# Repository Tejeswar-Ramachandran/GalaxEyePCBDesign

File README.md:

# GalaxEyePCBDesign
Internship Task for GalaxEye Space

GALAXEYE SPACE

INTERNSHIP TASK

Problem Statement:
1. You need to be able to convert inputs from up to 4 different digital I/O pins and get an output of 24 GPIO pins with a different logic level.
2. You need to design a neatly labeled schematic of this design and also generate a BOM with links to in-stock parts

Solution:

The Microcontroller will send out values at 3.3V level, from 4 different digital I/O pins. The output from these pins are passed through a level shifter to convert them to a different logic level. Once the logic level has been changed, the 4 output values are passed through 4 8 bit SIPO shift registers to obtain a total of 32 bits as output. Finally, 2 bits from each SIPO shift register were grounded to shorten the output to just 24 bits.

Assumptions:
1.	The Microcontroller input is directly given by the user. The Microcontroller reads it and directly passes it on to the Level Shifter without the requirement of any external processing.
2.	2 Bits from each SIPO Shift register were chosen and connected to the ground. An alternative would be to connect 8 bits from an entire shift register to bring down the output to 24 bits instead of 32 bits, but then we would have to ignore an input completely out of the 4 input bits.

Components:
1.	SIPO Shift Register – 74HC595D
2.	3.3V to 5V Logic Level Converter – Sparkfun Bi-Directional Logic Level Converter.

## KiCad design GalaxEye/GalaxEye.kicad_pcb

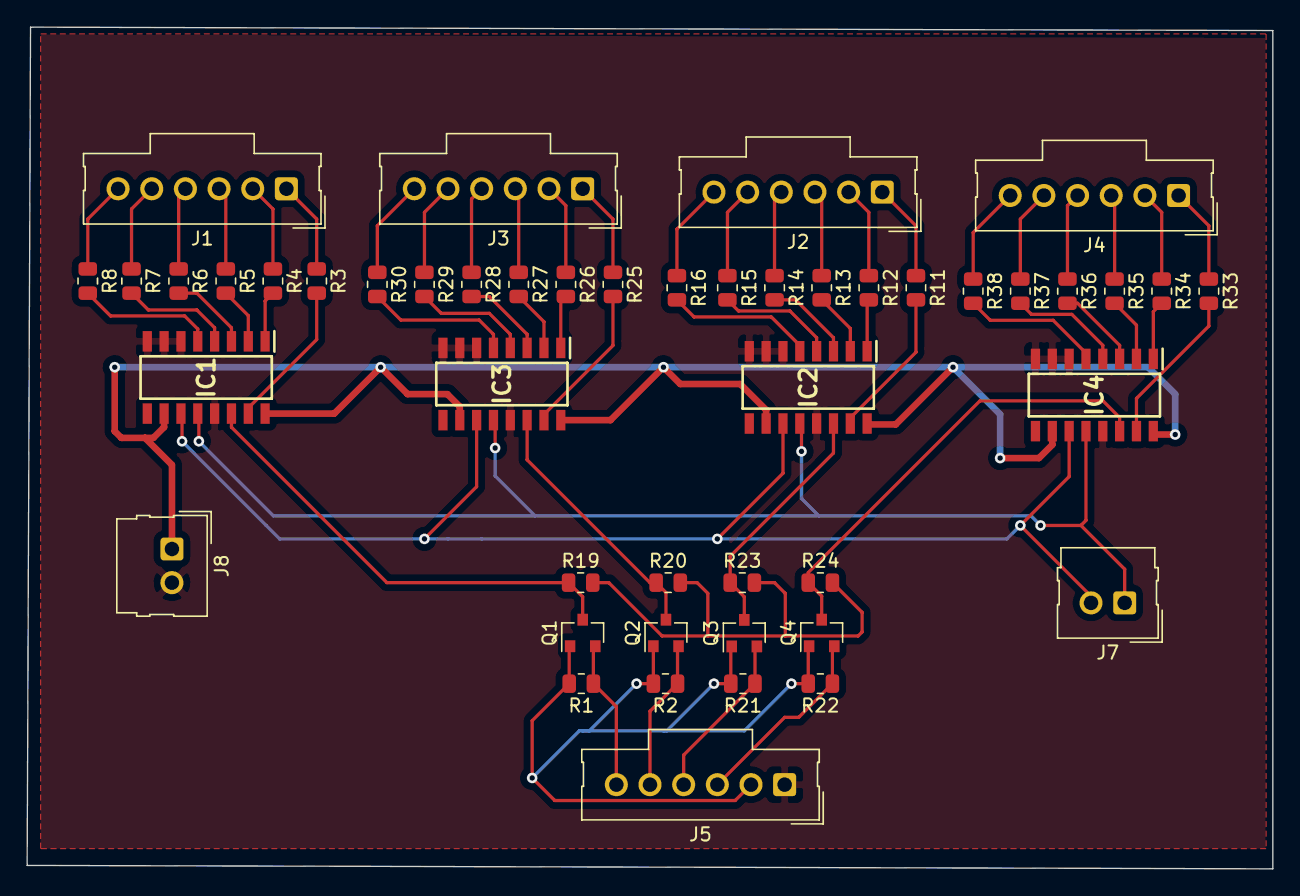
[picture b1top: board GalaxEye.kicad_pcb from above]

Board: 2 copper layers, 94.0 x 63.5 mm, 47 parts (0 on the bottom side), 62 nets.

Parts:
IC1, IC2, IC3, IC4: 74HC595D,118; SOIC127P600X175-16N
J1, J2, J3, J4, J5: Conn_01x06_Female; Molex_SL_171971-0006_1x06_P2.54mm_Vertical
J7, J8: Conn_01x02_Female; Molex_SL_171971-0002_1x02_P2.54mm_Vertical
Q1, Q2, Q3, Q4: BSS138; SOT-23
R1, R2, R3, R4, R5, R6, R7, R8, R11, R12, R13, R14, R15, R16, R19, R20, R21, R22, R23, R24, R25, R26, R27, R28, R29, R30, R33, R34, R35, R36, R37, R38: R; R_0805_2012Metric

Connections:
+5V: IC1.10, IC1.16, IC2.10, IC2.16, IC3.10, IC3.16, IC4.10, IC4.16, J8.1
/HV: R19.2, R20.2, R23.2, R24.2
/HV1: IC1.14, Q1.3, R19.1
/HV2: IC3.14, Q2.3, R20.1
/HV3: IC2.14, Q3.3, R23.1
/HV4: IC4.14, Q4.3, R24.1
/LV: J5.2, Q1.1, Q2.1, Q3.1, Q4.1, R1.2, R2.2, R21.2, R22.2
/LV1: J5.6, Q1.2, R1.1
/LV2: J5.5, Q2.2, R2.1
/LV3: J5.4, Q3.2, R21.1
/LV4: J5.3, Q4.2, R22.1
/SH_CP: IC1.11, IC2.11, IC3.11, IC4.11, J7.2
/ST_CP: IC1.12, IC2.12, IC3.12, IC4.12, J7.1
GND: IC1.6, IC1.7, IC1.8, IC1.13, IC2.6, IC2.7, IC2.8, IC2.13, IC3.6, IC3.7, IC3.8, IC3.13, IC4.6, IC4.7, IC4.8, IC4.13, J5.1, J8.2
unnamed: IC1.1, R4.2
unnamed: IC1.2, R5.2
unnamed: IC1.3, R6.2
unnamed: IC1.4, R7.2
unnamed: IC1.5, R8.2
unnamed: IC1.15, R3.2
unnamed: IC2.1, R12.2
unnamed: IC2.2, R13.2
unnamed: IC2.3, R14.2
unnamed: IC2.4, R15.2
unnamed: IC2.5, R16.2
unnamed: IC2.15, R11.2
unnamed: IC3.1, R26.2
unnamed: IC3.2, R27.2
unnamed: IC3.3, R28.2
unnamed: IC3.4, R29.2
unnamed: IC3.5, R30.2
unnamed: IC3.15, R25.2
unnamed: IC4.1, R34.2
unnamed: IC4.2, R35.2
unnamed: IC4.3, R36.2
unnamed: IC4.4, R37.2
unnamed: IC4.5, R38.2
unnamed: IC4.15, R33.2
unnamed: J1.1, R3.1
unnamed: J1.2, R4.1
unnamed: J1.3, R5.1
unnamed: J1.4, R6.1
unnamed: J1.5, R7.1
unnamed: J1.6, R8.1
unnamed: J2.1, R11.1
unnamed: J2.2, R12.1
unnamed: J2.3, R13.1
unnamed: J2.4, R14.1
unnamed: J2.5, R15.1
unnamed: J2.6, R16.1
unnamed: J3.1, R25.1
unnamed: J3.2, R26.1
unnamed: J3.3, R27.1
unnamed: J3.4, R28.1
unnamed: J3.5, R29.1
unnamed: J3.6, R30.1
unnamed: J4.1, R33.1
unnamed: J4.2, R34.1
unnamed: J4.3, R35.1
unnamed: J4.4, R36.1
unnamed: J4.5, R37.1
unnamed: J4.6, R38.1

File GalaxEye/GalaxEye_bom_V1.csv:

Component,Description,Part,References,Value,Footprint,Quantity Per PCB,Datasheet,Mouser Price/Stock,Mouser Part Number,Manufacturer_Name,Arrow Part Number,Height,Arrow Price/Stock,Manufacturer_Part_Number
1,"8-bit serial-in, serial or parallel-out shift register with output latches 3-state","74HC595D,118",IC1 IC2 IC3 IC4,"74HC595D,118",SOIC127P600X175-16N,4,https://assets.nexperia.com/documents/data-sheet/74HC_HCT595.pdf,https://www.mouser.co.uk/ProductDetail/Nexperia/74HC595D118?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,771-74HC595D-T,Nexperia,"74HC595D,118",1.75,https://www.arrow.com/en/products/74hc595d118/nexperia?regio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,"74HC595D,118"
2,"Generic connector, single row, 01x02, script generated (kicad-library-utils/schlib/autogen/connector/)",Conn_01x02_Female,J7 J8,Conn_01x02_Female,Molex_SL_171971-0002_1x02_P2.54mm_Vertical,2,~,,,,,,,
3,"Generic connector, single row, 01x06, script generated (kicad-library-utils/schlib/autogen/connector/)",Conn_01x06_Female,J1 J2 J3 J4 J5,Conn_01x06_Female,Molex_SL_171971-0006_1x06_P2.54mm_Vertical,5,~,,,,,,,
4,"50V Vds, 0.22A Id, N-Channel MOSFET, SOT-23",BSS138,Q1 Q2 Q3 Q4,BSS138,SOT-23,4,https://www.onsemi.com/pub/Collateral/BSS138-D.PDF,,,,,,,
5,Resistor,R,R3 R4 R5 R6 R7 R8 R11 R12 R13 R14 R15 R16 R25 R26 R27 R28 R29 R30 R33 R34 R35 R36 R37 R38,1k,R_0805_2012Metric,24,~,,,,,,,
6,Resistor,R,R1 R2 R19 R20 R21 R22 R23 R24,10k,R_0805_2012Metric,8,~,,,,,,,





Component Groups:,6
Component Count:,47
Fitted Components:,47
Number of PCBs:,1
Total components:,47
Schematic Version:,V1
Schematic Date:,2023-01-22
PCB Variant:,udefault
BoM Date:,01/23/23 21:36:17
Schematic Source:,GalaxEye.sch
KiCad Version:,Eeschema (5.1.10)-1
